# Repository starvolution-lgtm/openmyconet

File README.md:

# OpenMycoNet

Ein Citizen-Science-Projekt im Aufbau: ein weltweit vernetzbares System zur Erfassung
bioelektrischer Signale aus Mykorrhiza- und Pilznetzwerken. Die Aktivität ist messbar — die
Frage ist, was ihre Muster bedeuten.

Website: <https://www.openmyconet.de> · Kontakt und Rechtliches: [Impressum](https://www.openmyconet.de/impressum.html)

Dieses Repository enthält die Software. Diese Seite erklärt für Menschen, wie sie aufgebaut ist
und wie an ihr gearbeitet wird; technische Details stehen in den verlinkten Dateien.

## Was wo liegt

| Teil | Ordner | Was es tut |
|---|---|---|
| **Server** | [`openmyconet_server/`](openmyconet_server/) | Website (fünfsprachig), Anmeldung und Dashboard, Förderer, Chatbot, Datenlabor mit simulierten Daten, Empfang und Prüfung der Messdaten, Verwaltung |
| **Firmware** | [`firmware/`](firmware/README.md) | Software für die Messknoten. Bisher fertig: das Erzeugen, Absichern und Signieren der Datenpakete |
| **Automatische Prüfungen** | [`.github/workflows/`](.github/workflows/) | Tests bei jeder Änderung, Erreichbarkeit der Website alle 15 Minuten |

Nicht hier: die Projektsteuerung (Pläne, Status, Partner, Gebrauchsmuster) liegt bewusst in
einem lokalen, nicht öffentlichen Kontrollzentrum mit eigener verschlüsselter Sicherung.

```mermaid
flowchart LR
    K[Messknoten<br/>ESP32-S3] -- LoRa --> B[Bridge]
    B -- HTTPS, eigener Schlüssel --> S[Server<br/>Flask + PostgreSQL]
    K -. microSD-Import .-> S
    S --> W[Website + Datenlabor]
    S --> D[(Datenbank<br/>sandbox / live)]
    D --> SB[(Sicherung extern,<br/>verschlüsselt)]
```

## Wie eine Änderung entsteht

```mermaid
flowchart LR
    A[Idee / Auftrag] --> C[Code + Tests<br/>lokal grün]
    C --> P[Push auf main]
    P --> CI{Automatische<br/>Prüfungen}
    CI -- rot --> C
    CI -- grün --> ST[Staging<br/>Testumgebung]
    ST --> PR[Produktion<br/>mit Backup + Rückfallweg]
```

1. **Lokal:** Code und Tests entstehen zusammen; alle Tests müssen vor dem Hochladen grün sein.
2. **Automatische Prüfungen bei jedem Push** (GitHub Actions):
   - die komplette Testsuite, einmal mit SQLite und einmal mit PostgreSQL wie im Betrieb,
   - Code-Stil, Sicherheits-Scan des Codes, bekannte Lücken in verwendeten Paketen,
   - Barrierefreiheit, Suchmaschinen-Tauglichkeit und Qualität aller öffentlichen Seiten,
   - Firmware: Normtests der Kryptografie, die Paket-Testvektoren Byte für Byte, und ein
     Kreuztest, bei dem der Server Pakete aus der Firmware liest und nachrechnet.
3. **Staging:** eine vollständige Testumgebung auf demselben Server, eigene Datenbank, verschickt
   nie echte Mails.
4. **Produktion:** nur möglich, wenn die Prüfungen für genau diesen Stand grün sind und Staging
   ihn hat. Vor jedem Datenbank-Umbau wird gesichert; antwortet die Seite danach nicht, wird der
   alte Code automatisch zurückgespielt.

## Sicherheit, in Schichten

- **Website:** Schutz gegen untergeschobene Formulare (CSRF) und eingeschleusten Code (strenge
  Content-Security-Policy), Zwei-Faktor-Anmeldung für die Verwaltung, Begrenzung von
  Wiederholungsversuchen, geprüfte Uploads.
- **Messdaten:** Jedes Paket trägt Prüfsummen, die eine Kette bilden (Lücken und Änderungen
  fallen auf), und eine Signatur des Messknotens (Ed25519); der Server kennt nur öffentliche
  Schlüssel. Datenbank-Rollen sind getrennt: Die Website kann Messdaten weder löschen noch
  genaue Standorte lesen. Strittige Daten werden nie stillschweigend verworfen, sondern
  aufbewahrt.
- **Betrieb:** Zugang zum Server nur mit Schlüssel, Firewall, tägliche verschlüsselte
  Sicherungen außer Haus mit automatischer Wiederherstellungsprobe, Überwachung von außen.
- **Datenschutz:** feste Löschfristen werden automatisch durchgesetzt und stehen so in der
  Datenschutzerklärung.

## Anpassungsfähigkeit

- **Datenbank-Änderungen** laufen als nachvollziehbare Migrationen; ein Test stellt sicher, dass
  Code und Datenbank nie auseinanderlaufen.
- **Versionierte Formate:** Datenpakete und Datenbank-Schemas tragen Versionsnummern; neue
  Versionen kommen hinzu, ohne alte Daten unlesbar zu machen.
- **Simulation und echte Messungen** laufen durch dieselbe Verarbeitung, aber in getrennten
  Bereichen (`sandbox` / `live`).
- **Die Firmware-Kernbibliothek** ist plattformunabhängig und wird auf dem PC gegen den Server
  geprüft — lange bevor eine Platine da ist.

## Für Entwickler

- Server: [`openmyconet_server/CLAUDE.md`](openmyconet_server/CLAUDE.md) (Aufbau, Regeln,
  Tests, Deploy) und die Themen-Dateien in [`openmyconet_server/docs/claude/`](openmyconet_server/docs/claude/)
- Datenpaket-Format: [`openmyconet_server/docs/dateneingang_format_v1.md`](openmyconet_server/docs/dateneingang_format_v1.md)
- Empfangsweg für Bridges: [`openmyconet_server/docs/dateneingang_empfang.md`](openmyconet_server/docs/dateneingang_empfang.md)
- Firmware: [`firmware/README.md`](firmware/README.md)

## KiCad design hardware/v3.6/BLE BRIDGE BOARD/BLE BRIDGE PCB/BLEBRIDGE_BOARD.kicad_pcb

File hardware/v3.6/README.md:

# Hardware V3.6 (fertigungsreif)

Finaler Stand der beiden Platinen **COMBO NODE** (Messknoten) und **BLE BRIDGE**,
Version 3.6 (KiCad-Projekte, Fertigungsdateien, Prüfberichte). Abgelegt am 26.10.2026.

Quelle: Paket `OpenMyCoNet_Project_Completed_Package_Finale_Ver3.6.zip`
(SHA-256 `373a08654455d4fddd7a3f6c591d7695429d6e759cf8f633c875d926a3661b07`),
unverändert entpackt. Weggelassen wurde nur der interne KiCad-Verlauf
`BLE BRIDGE BOARD/BLE BRIDGE PCB/.history/` (ein eingebettetes Git-Verzeichnis vom Juni 2026).

## Für die Bestellung

**Diese beiden BOMs verwenden**, nicht die `bom.csv` in den Unterordnern:

| Datei | Unterschied zur `bom.csv` im Paket |
|---|---|
| `COMBO_NODE_V3.6_bom_korrigiert.csv` | 100 nF (0603): Menge 20 statt 19 (C51 war nicht mitgezählt) |
| `BLEBRIDGE_V3.6_bom_korrigiert.csv` | 10 kΩ (0603): Menge 10 statt 11 (nach Wegfall des zweiten R13) |

Sonst sind die Dateien Zeile für Zeile gleich. Gegengeprüft (26.10.2026): Jede Zeile hat
so viele Bezeichner wie ihre Menge (Node 179, Bridge 99 Bauteile), BOM und
Bestückungsliste (`positions.csv`) enthalten auf beiden Platinen genau dieselben Bauteile.

Gerber und Bohrdaten: `COMBO NODE BOARD/PRODUCTION FILES/production/COMBO_NODE_3.6.zip`
und `BLE BRIDGE BOARD/PRODUCTION FILES/production/BLEBRIDGE_BOARD.zip`.

## Änderungen gegenüber dem Stand vom 23.10.2026

Laut Prüfung (Vergleich der Verdrahtung Pin für Pin, BOM, Bestückungsliste, Layout und Gerber):

- **Node, Puffer:** neuer Baustein U19 (OPA333, SOT-23-5, ca. 17 µA Ruhestrom) als
  Spannungsfolger: Eingang am Teiler R43/R44 (C34), Ausgang über R62 an den Referenzknoten,
  Abblockkondensator C51. U13B arbeitet nur noch für den EC-Empfang, die EC-Messung wird
  nicht mehr verfälscht. In der Netzliste nachvollzogen: U19 Pin 5 an 3.3VA, Pin 2 an GND,
  Pin 3 (+IN) am Teiler, Pin 1 (OUT) und Pin 4 (−IN) verbunden und an R62.
- **Bridge, R13:** nur noch ein R13 (1,18 kΩ an ILIM des BQ24075). Der zweite Widerstand
  an SYSOFF ist entfallen; er zog in der Stellung „Aus“ dauerhaft ca. 0,4 mA aus dem Akku.
  SYSOFF legt der Schalter S1 fest.
- Prüfbericht V3.6: `GUIDE/OpenMycoNet_Architectural_Evolution_Design_Verification_Report_V3.6.docx`.

## Wichtig: TH1 und der Akku

TH1 (10-kΩ-NTC) ist auf **beiden** Platinen nicht bestückt (fehlt in BOM und
Bestückungsliste, steht im Schaltplan aber noch als bestückt, in `designators.csv`
ebenfalls noch aufgeführt). TH1 liegt am TS-Pin des Ladereglers BQ24075 (U4, Pin 1),
an derselben Leitung wie **Pin 2 des Akkusteckers J2** (Belegung +BATT / NTC / GND).

Ohne TH1 misst der Laderegler die Temperatur über den Akkupack. Deshalb:

- **Akkus müssen 3-adrig sein, mit 10-kΩ-NTC (B ≈ 3435) an der mittleren Ader.**
- Ein Akku mit nur 2 Adern lässt TS offen: Der BQ24075 sieht einen Temperaturfehler und
  **lädt nicht**. Dann TH1 bzw. einen festen 10-kΩ-Widerstand doch bestücken.
- Firmware: Die Node misst keine eigene Platinentemperatur. Die Ausgänge CHG und PGOOD
  des BQ24075 hängen auf beiden Platinen nur an Pull-ups (R15/R16), **nicht am ESP32**
  (Netzliste geprüft 27.10.2026). Die Firmware sieht nur die Laderate des MAX17048
  (positiv = lädt) und meldet „lädt“ bzw. „lädt nicht“ im Protokoll. Für eine spätere
  Revision: CHG an einen freien Eingang führen.

## BQ24075: zwei LCSC-Nummern (geklärt)

Der BQ24075 (U4) hat in den beiden BOMs verschiedene LCSC-Nummern: Node `C15464`, Bridge
`C2865459`. Laut Richard (27.10.2026) beabsichtigt: Die Suffixe RGTR und RGTT unterscheiden
nur die Verpackung (Rollengröße), Footprint und Pads sind gleich. Beide Nummern sind für ihre
Platine richtig, die BOMs bleiben so.

## Pin-Merkblatt Firmware (Watchdog, Akkualarm)

`BioComm_Bridge_V3.6_Pinbelegung_Firmware.md` (Stand 27.10.2026), unverändert abgelegt.
Gegen die Netzlisten V3.6 geprüft (27.10.2026), alle Angaben stimmen
(Modul-Pin → GPIO nach Datenblatt ESP32-S3-WROOM-1):

| Signal | Node | Bridge | Netz in der Netzliste |
|---|---|---|---|
| BATT_ALERT | GPIO21 (U6-23) | GPIO47 (U6-24) | MAX17048 U5-5 (ALRT), Pull-up Node R20 / Bridge R32 (10 kΩ), Bridge zusätzlich D3 |
| WCD_SLEEP | GPIO47 (U6-24) | GPIO48 (U6-25) | TPS3851 U7-5 (SET1), Pull-down Node R55 / Bridge R27 (100 kΩ) |
| RST_WDI | GPIO4 (U6-4) | GPIO21 (U6-23) | TPS3851 U7-6 (WDI) |
| LED_ON | – | GPIO41 (U6-34) | über R23 (1 kΩ) an D7 |

Ergänzung für die **Node-Firmware**: Auch die Node hat den TPS3851H33 mit 100 nF an CWD
(C20). Ist ihr Watchdog über GPIO47 eingeschaltet, gilt dort dasselbe Zeitfenster von
rund 323 ms (GPIO4 etwa alle 300 ms umschalten oder vorher abschalten).

## Inhalt

| Ordner | Inhalt |
|---|---|
| `COMBO NODE BOARD/COMBO_NODE/` | KiCad-Projekt Node (Schaltplan-Blätter, Layout) |
| `COMBO NODE BOARD/PRODUCTION FILES/` | Gerber-Zip, BOM, Bestückungsliste, Netzliste (IPC), interaktive BOM, Kaufhinweise für Ersatzteile |
| `COMBO NODE BOARD/REPORTATION/` | Schaltplan-PDF, ERC/DRC-Ergebnisse, Unterlagen zum Watchdog TPS3851 |
| `COMBO NODE BOARD/DOCUMENTATION/` | Bilder der Lagen und Ansichten |
| `BLE BRIDGE BOARD/…` | dasselbe für die Bridge |
| `GUIDE/` | ERC/DRC-Leitfäden beider Platinen, Prüfbericht V3.6 |

Nicht Teil des Deploys: Der Server bekommt nur `openmyconet_server/`.

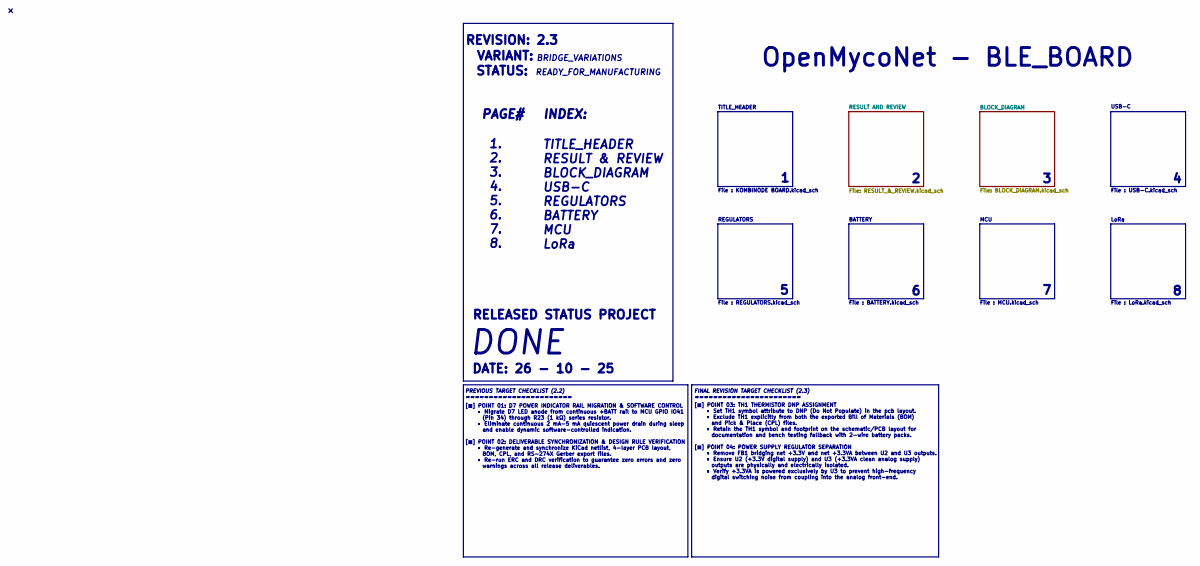
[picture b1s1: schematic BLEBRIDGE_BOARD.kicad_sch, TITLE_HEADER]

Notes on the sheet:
REGULATORS
File : MCU.kicad_sch
File : USB-C.kicad_sch
BATTERY
PAGE#
File : LoRa.kicad_sch
DONE
MCU
File : KOMBINODE BOARD.kicad_sch
USB-C
OpenMycoNet - BLE_BOARD
LoRa
PREVIOUS TARGET CHECKLIST (2.2) =======================
RELEASED STATUS PROJECT
DATE: 26 - 10 - 25
[■] POINT 03: TH1 THERMISTOR DNP ASSIGNMENT • Set TH1 symbol attribute to DNP (Do Not Populate) in the pcb layout. • Exclude TH1 explicitly from both the exported Bill of Materials (BOM) and Pick & Place (CPL) files. • Retain the TH1 symbol and footprint on the schematic/PCB layout for documentatio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
1. 2. 3. 4. 5. 6. 7. 8.
READY_FOR_MANUFACTURING
File : BATTERY.kicad_sch
VARIANT:
REVISION: 2.3
TITLE_HEADER RESULT & REVIEW BLOCK_DIAGRAM USB-C REGULATORS BATTERY MCU LoRa
BRIDGE_VARIATIONS
[■] POINT 01: D7 POWER INDICATOR RAIL MIGRATION & SOFTWARE CONTROL • Migrate D7 LED anode from continuous +BATT rail to MCU GPIO IO41 (Pin 34) through R23 (1 kΩ) series resistor. • Eliminate continuous 2 mA-5 mA quiescent power drain during sleep and enable dynamic software-controlled indication. [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
FINAL REVISION TARGET CHECKLIST (2.3) =======================
STATUS:
TITLE_HEADER
INDEX:
File : REGULATORS.kicad_sch

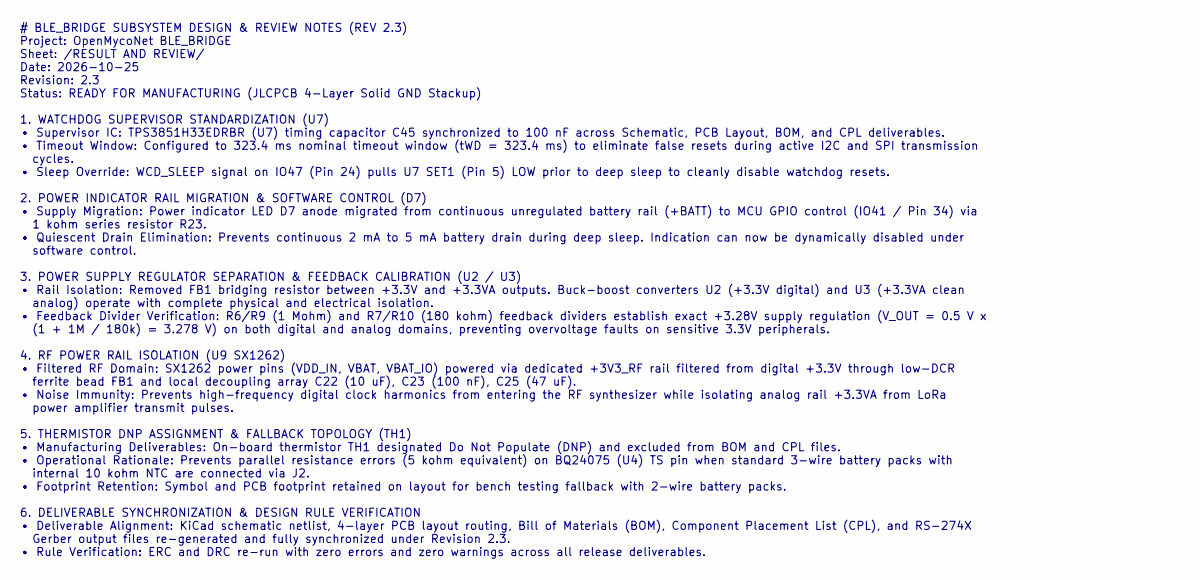
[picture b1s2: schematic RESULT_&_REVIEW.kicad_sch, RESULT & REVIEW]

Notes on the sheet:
# BLE_BRIDGE SUBSYSTEM DESIGN & REVIEW NOTES (REV 2.3) Project: OpenMycoNet BLE_BRIDGE Sheet: /RESULT AND REVIEW/ Date: 2026-10-25 Revision: 2.3 Status: READY FOR MANUFACTURING (JLCPCB 4-Layer Solid GND Stackup) 1. WATCHDOG SUPERVISOR STANDARDIZATION (U7) • Supervisor IC: TPS3851H33EDRBR (U7) timin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

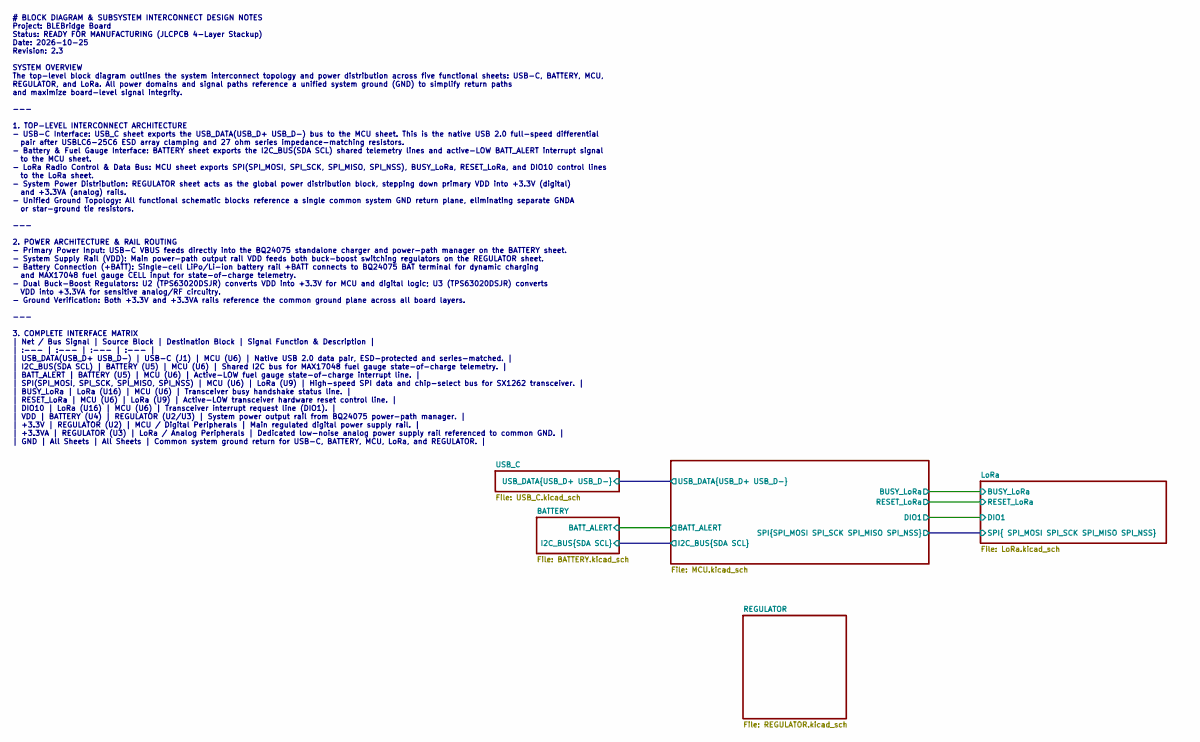
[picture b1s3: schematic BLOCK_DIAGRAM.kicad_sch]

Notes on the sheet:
# BLOCK DIAGRAM & SUBSYSTEM INTERCONNECT DESIGN NOTES Project: BLEBridge Board Status: READY FOR MANUFACTURING (JLCPCB 4-Layer Stackup) Date: 2026-10-25 Revision: 2.3 SYSTEM OVERVIEW The top-level block diagram outlines the system interconnect topology and power distribution across five functional 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

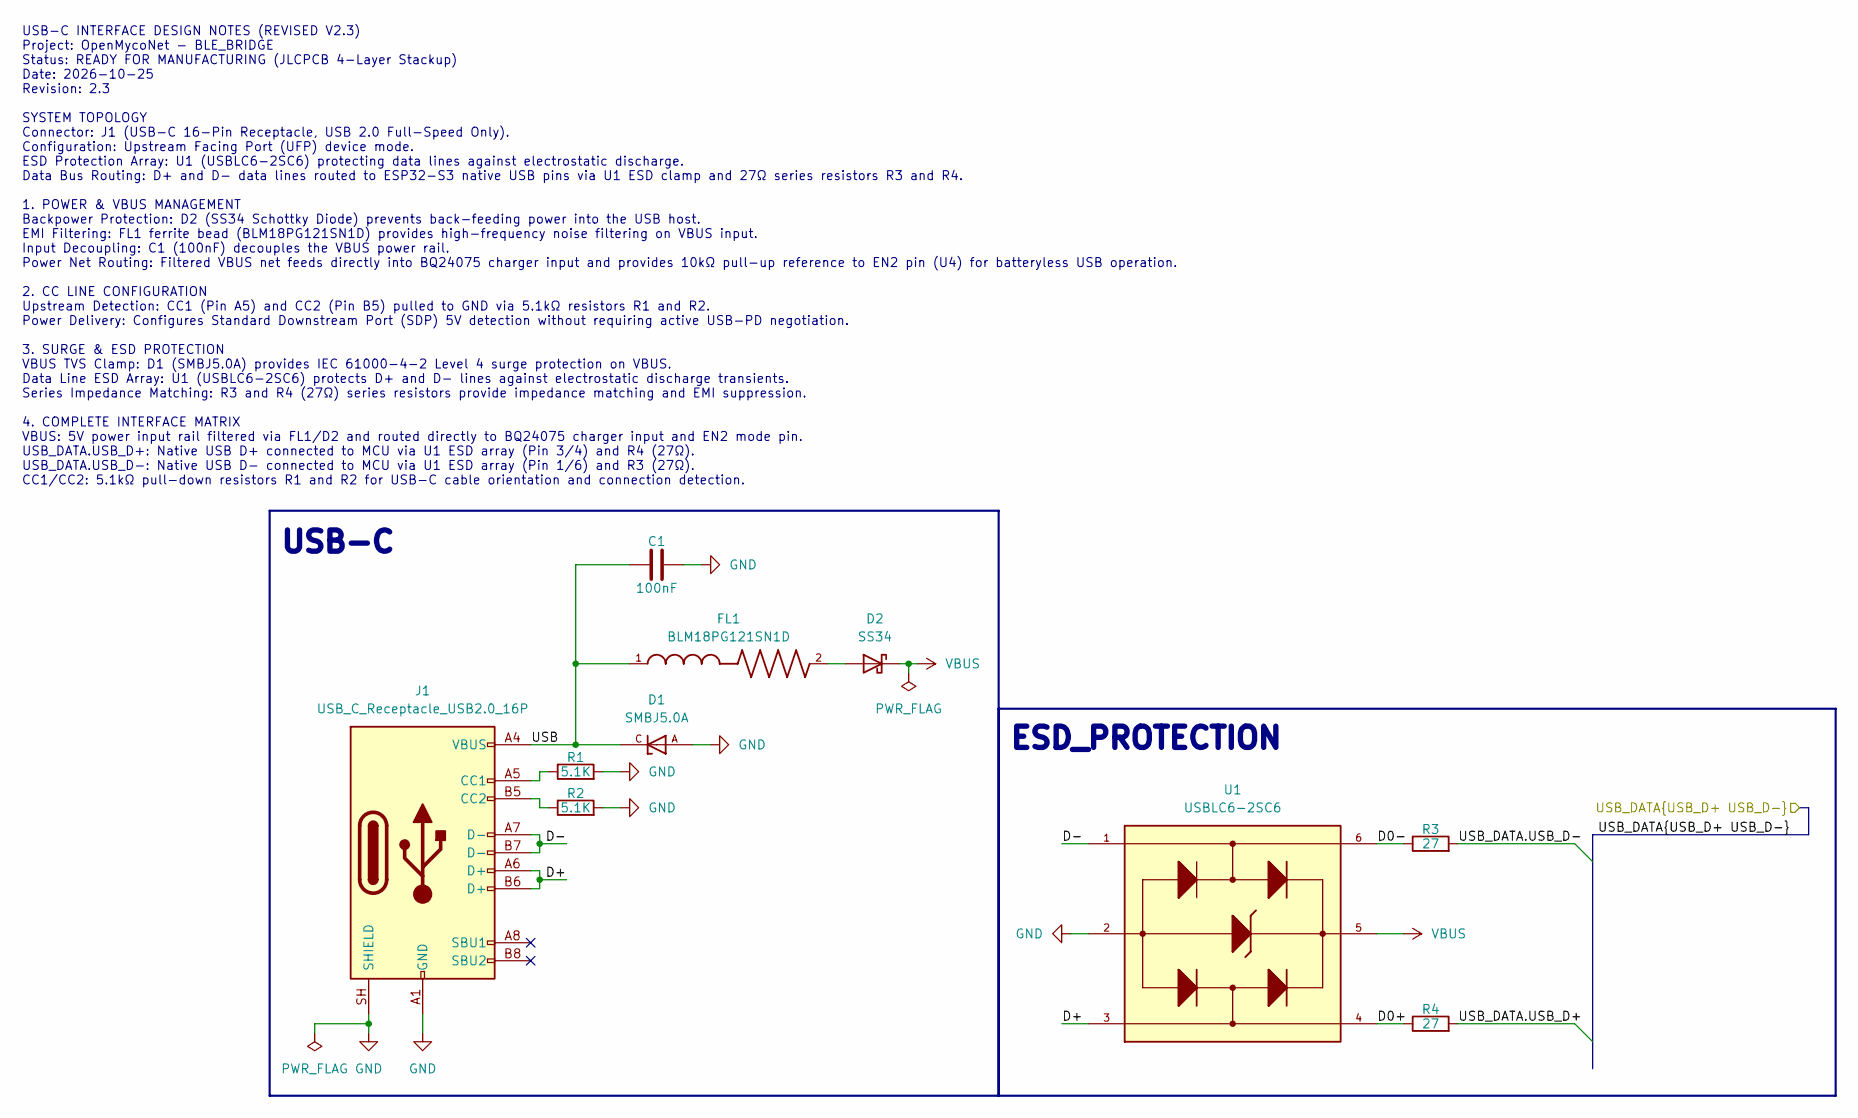
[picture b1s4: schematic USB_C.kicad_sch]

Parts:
C1: 100nF; C_0603_1608Metric
D1: SMBJ5.0A; PARTREV F2102
D2: SS34; D_SMA
FL1: BLM18PG121SN1D; BEADC1608X95N
J1: USB_C_Receptacle_USB2.0_16P; USB_C_Receptacle_GCT_USB4105-xx-A_16P_TopMnt_Horizontal
R1, R2: 5.1K; R_0402_1005Metric
R3, R4: 27; R_0402_1005Metric
U1: USBLC6-2SC6

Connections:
/BLOCK_DIAGRAM//USB_DATA.USB_D+: R4.2; also elsewhere on the board
/BLOCK_DIAGRAM//USB_DATA.USB_D-: R3.2; also elsewhere on the board
/BLOCK_DIAGRAM/USB_C/D0+: R4.1, U1.4
/BLOCK_DIAGRAM/USB_C/D0-: R3.1, U1.6
/BLOCK_DIAGRAM/USB_C/D+: J1.A6 (D+), J1.B6 (D+), U1.3
/BLOCK_DIAGRAM/USB_C/D-: J1.A7 (D-), J1.B7 (D-), U1.1
/BLOCK_DIAGRAM/USB_C/USB: C1.1, D1.C, FL1.1, J1.A4 (VBUS), J1.A9 (VBUS), J1.B4 (VBUS), J1.B9 (VBUS)
GND: C1.2, D1.A, J1.A1 (GND), J1.A12 (GND), J1.B1 (GND), J1.B12 (GND), J1.SH (SHIELD), R1.2, R2.2, U1.2; also elsewhere on the board
unnamed: D2.2 (A), FL1.2
unnamed: J1.A5 (CC1), R1.1
unnamed: J1.B5 (CC2), R2.1
VBUS: D2.1 (K), U1.5; also elsewhere on the board

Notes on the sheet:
USB-C INTERFACE DESIGN NOTES (REVISED V2.3) Project: OpenMycoNet - BLE_BRIDGE Status: READY FOR MANUFACTURING (JLCPCB 4-Layer Stackup) Date: 2026-10-25 Revision: 2.3 SYSTEM TOPOLOGY Connector: J1 (USB-C 16-Pin Receptacle, USB 2.0 Full-Speed Only). Configuration: Upstream Facing Port (UFP) device mo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
ESD_PROTECTION
USB-C

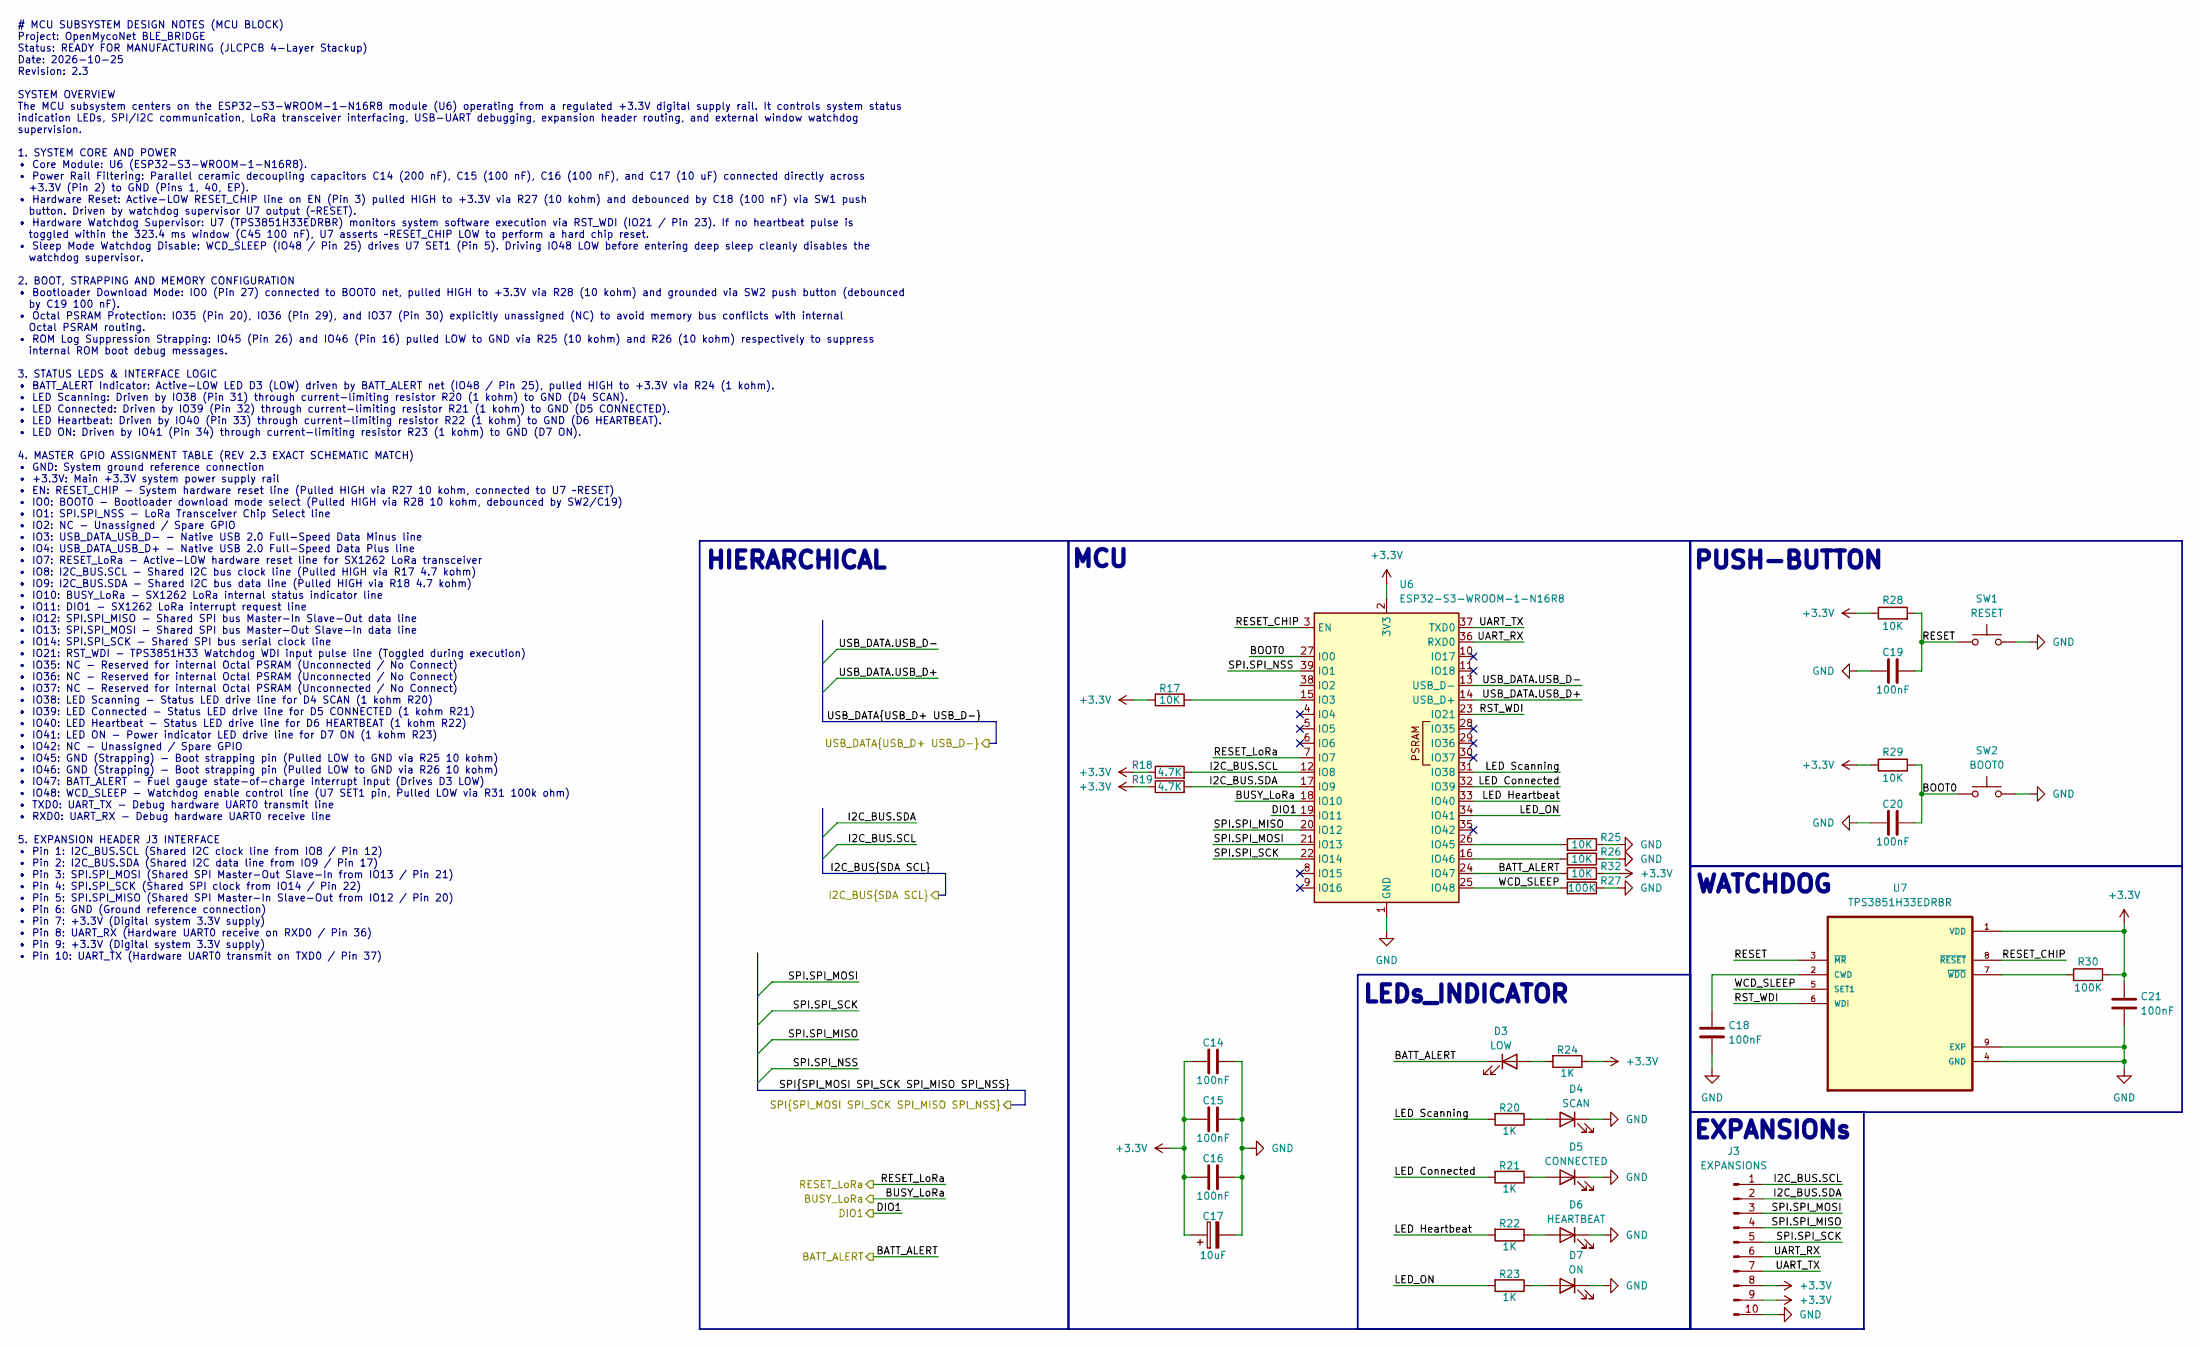
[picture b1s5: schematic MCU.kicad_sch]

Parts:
C14, C15, C16, C18, C19, C20, C21: 100nF; C_0603_1608Metric
C17: 10uF; CP_EIA-3216-18_Kemet-A
D3: LOW; LED_1206_3216Metric
D4: SCAN; LED_1206_3216Metric
D5: CONNECTED; LED_1206_3216Metric
D6: HEARTBEAT; LED_1206_3216Metric
D7: ON; LED_1206_3216Metric
J3: EXPANSIONS; PinHeader_2x05_P2.54mm_Vertical_SMD
R17, R25, R26, R28, R29, R32: 10K; R_0603_1608Metric
R18, R19: 4.7K; R_0603_1608Metric
R20, R21, R22, R23, R24: 1K; R_0603_1608Metric
R27, R30: 100K; R_0603_1608Metric
SW1: RESET; SW_SPST_B3U-1000P
SW2: BOOT0; SW_SPST_B3U-1000P
U6: ESP32-S3-WROOM-1-N16R8; ESP32-S3-WROOM-1
U7: TPS3851H33EDRBR; IC_DRV8601DRBT

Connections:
+3.3V: C14.1, C15.1, C16.1, C17.1, C21.1, J3.8, J3.9, R17.1, R18.1, R19.1, R24.1, R28.1, R29.1, R30.2, R32.1, U6.2 (3V3), U7.1 (VDD); also elsewhere on the board
/BLOCK_DIAGRAM//BATT_ALERT: D3.1 (K), R32.2, U6.24 (IO47); also elsewhere on the board
/BLOCK_DIAGRAM//BOOT0: C20.2, R29.2, SW2.1, U6.27 (IO0)
/BLOCK_DIAGRAM//BUSY_LoRa: U6.18 (IO10); also elsewhere on the board
/BLOCK_DIAGRAM//DIO1: U6.19 (IO11); also elsewhere on the board
/BLOCK_DIAGRAM//I2C_BUS.SCL: J3.1, R18.2, U6.12 (IO8); also elsewhere on the board
/BLOCK_DIAGRAM//I2C_BUS.SDA: J3.2, R19.2, U6.17 (IO9); also elsewhere on the board
/BLOCK_DIAGRAM//LED Connected: R21.2, U6.32 (IO39)
/BLOCK_DIAGRAM//LED Heartbeat: R22.2, U6.33 (IO40)
/BLOCK_DIAGRAM//LED Scanning: R20.2, U6.31 (IO38)
/BLOCK_DIAGRAM//LED_ON: R23.2, U6.34 (IO41)
/BLOCK_DIAGRAM//RESET: C19.2, R28.2, SW1.1, U7.3 (~MR)
/BLOCK_DIAGRAM//RESET_CHIP: U6.3 (EN), U7.8 (~RESET)
/BLOCK_DIAGRAM//RESET_LoRa: U6.7 (IO7); also elsewhere on the board
/BLOCK_DIAGRAM//RST_WDI: U6.23 (IO21), U7.6 (WDI)
/BLOCK_DIAGRAM//SPI.SPI_MISO: J3.4, U6.20 (IO12); also elsewhere on the board
/BLOCK_DIAGRAM//SPI.SPI_MOSI: J3.3, U6.21 (IO13); also elsewhere on the board
/BLOCK_DIAGRAM//SPI.SPI_NSS: U6.39 (IO1); also elsewhere on the board
/BLOCK_DIAGRAM//SPI.SPI_SCK: J3.5, U6.22 (IO14); also elsewhere on the board
/BLOCK_DIAGRAM//UART_RX: J3.6, U6.36 (RXD0)
/BLOCK_DIAGRAM//UART_TX: J3.7, U6.37 (TXD0)
/BLOCK_DIAGRAM//USB_DATA.USB_D+: U6.14 (USB_D+); also elsewhere on the board
/BLOCK_DIAGRAM//USB_DATA.USB_D-: U6.13 (USB_D-); also elsewhere on the board
/BLOCK_DIAGRAM//WCD_SLEEP: R27.2, U6.25 (IO48), U7.5 (SET1)
GND: C14.2, C15.2, C16.2, C17.2, C18.2, C19.1, C20.1, C21.2, D4.1 (K), D5.1 (K), D6.1 (K), D7.1 (K), J3.10, R25.1, R26.1, R27.1, SW1.2, SW2.2, U6.1 (GND), U6.40 (GND), U6.41 (GND), U7.4 (GND), U7.9 (EXP), U7.10 (EXP), U7.11 (EXP), U7.12 (EXP), U7.13 (EXP); also elsewhere on the board
unnamed: D3.2 (A), R24.2
unnamed: D4.2 (A), R20.1
unnamed: D5.2 (A), R21.1
unnamed: D6.2 (A), R22.1
unnamed: D7.2 (A), R23.1
unnamed: R17.2, U6.15 (IO3)
unnamed: R25.2, U6.26 (IO45)
unnamed: R26.2, U6.16 (IO46)
unnamed: C18.1, U7.2 (CWD)
unnamed: R30.1, U7.7 (~WDO)

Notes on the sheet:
WATCHDOG
HIERARCHICAL
PUSH-BUTTON
EXPANSIONs
# MCU SUBSYSTEM DESIGN NOTES (MCU BLOCK) Project: OpenMycoNet BLE_BRIDGE Status: READY FOR MANUFACTURING (JLCPCB 4-Layer Stackup) Date: 2026-10-25 Revision: 2.3 SYSTEM OVERVIEW The MCU subsystem centers on the ESP32-S3-WROOM-1-N16R8 module (U6) operating from a regulated +3.3V digital supply rail. 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
LEDs_INDICATOR
MCU

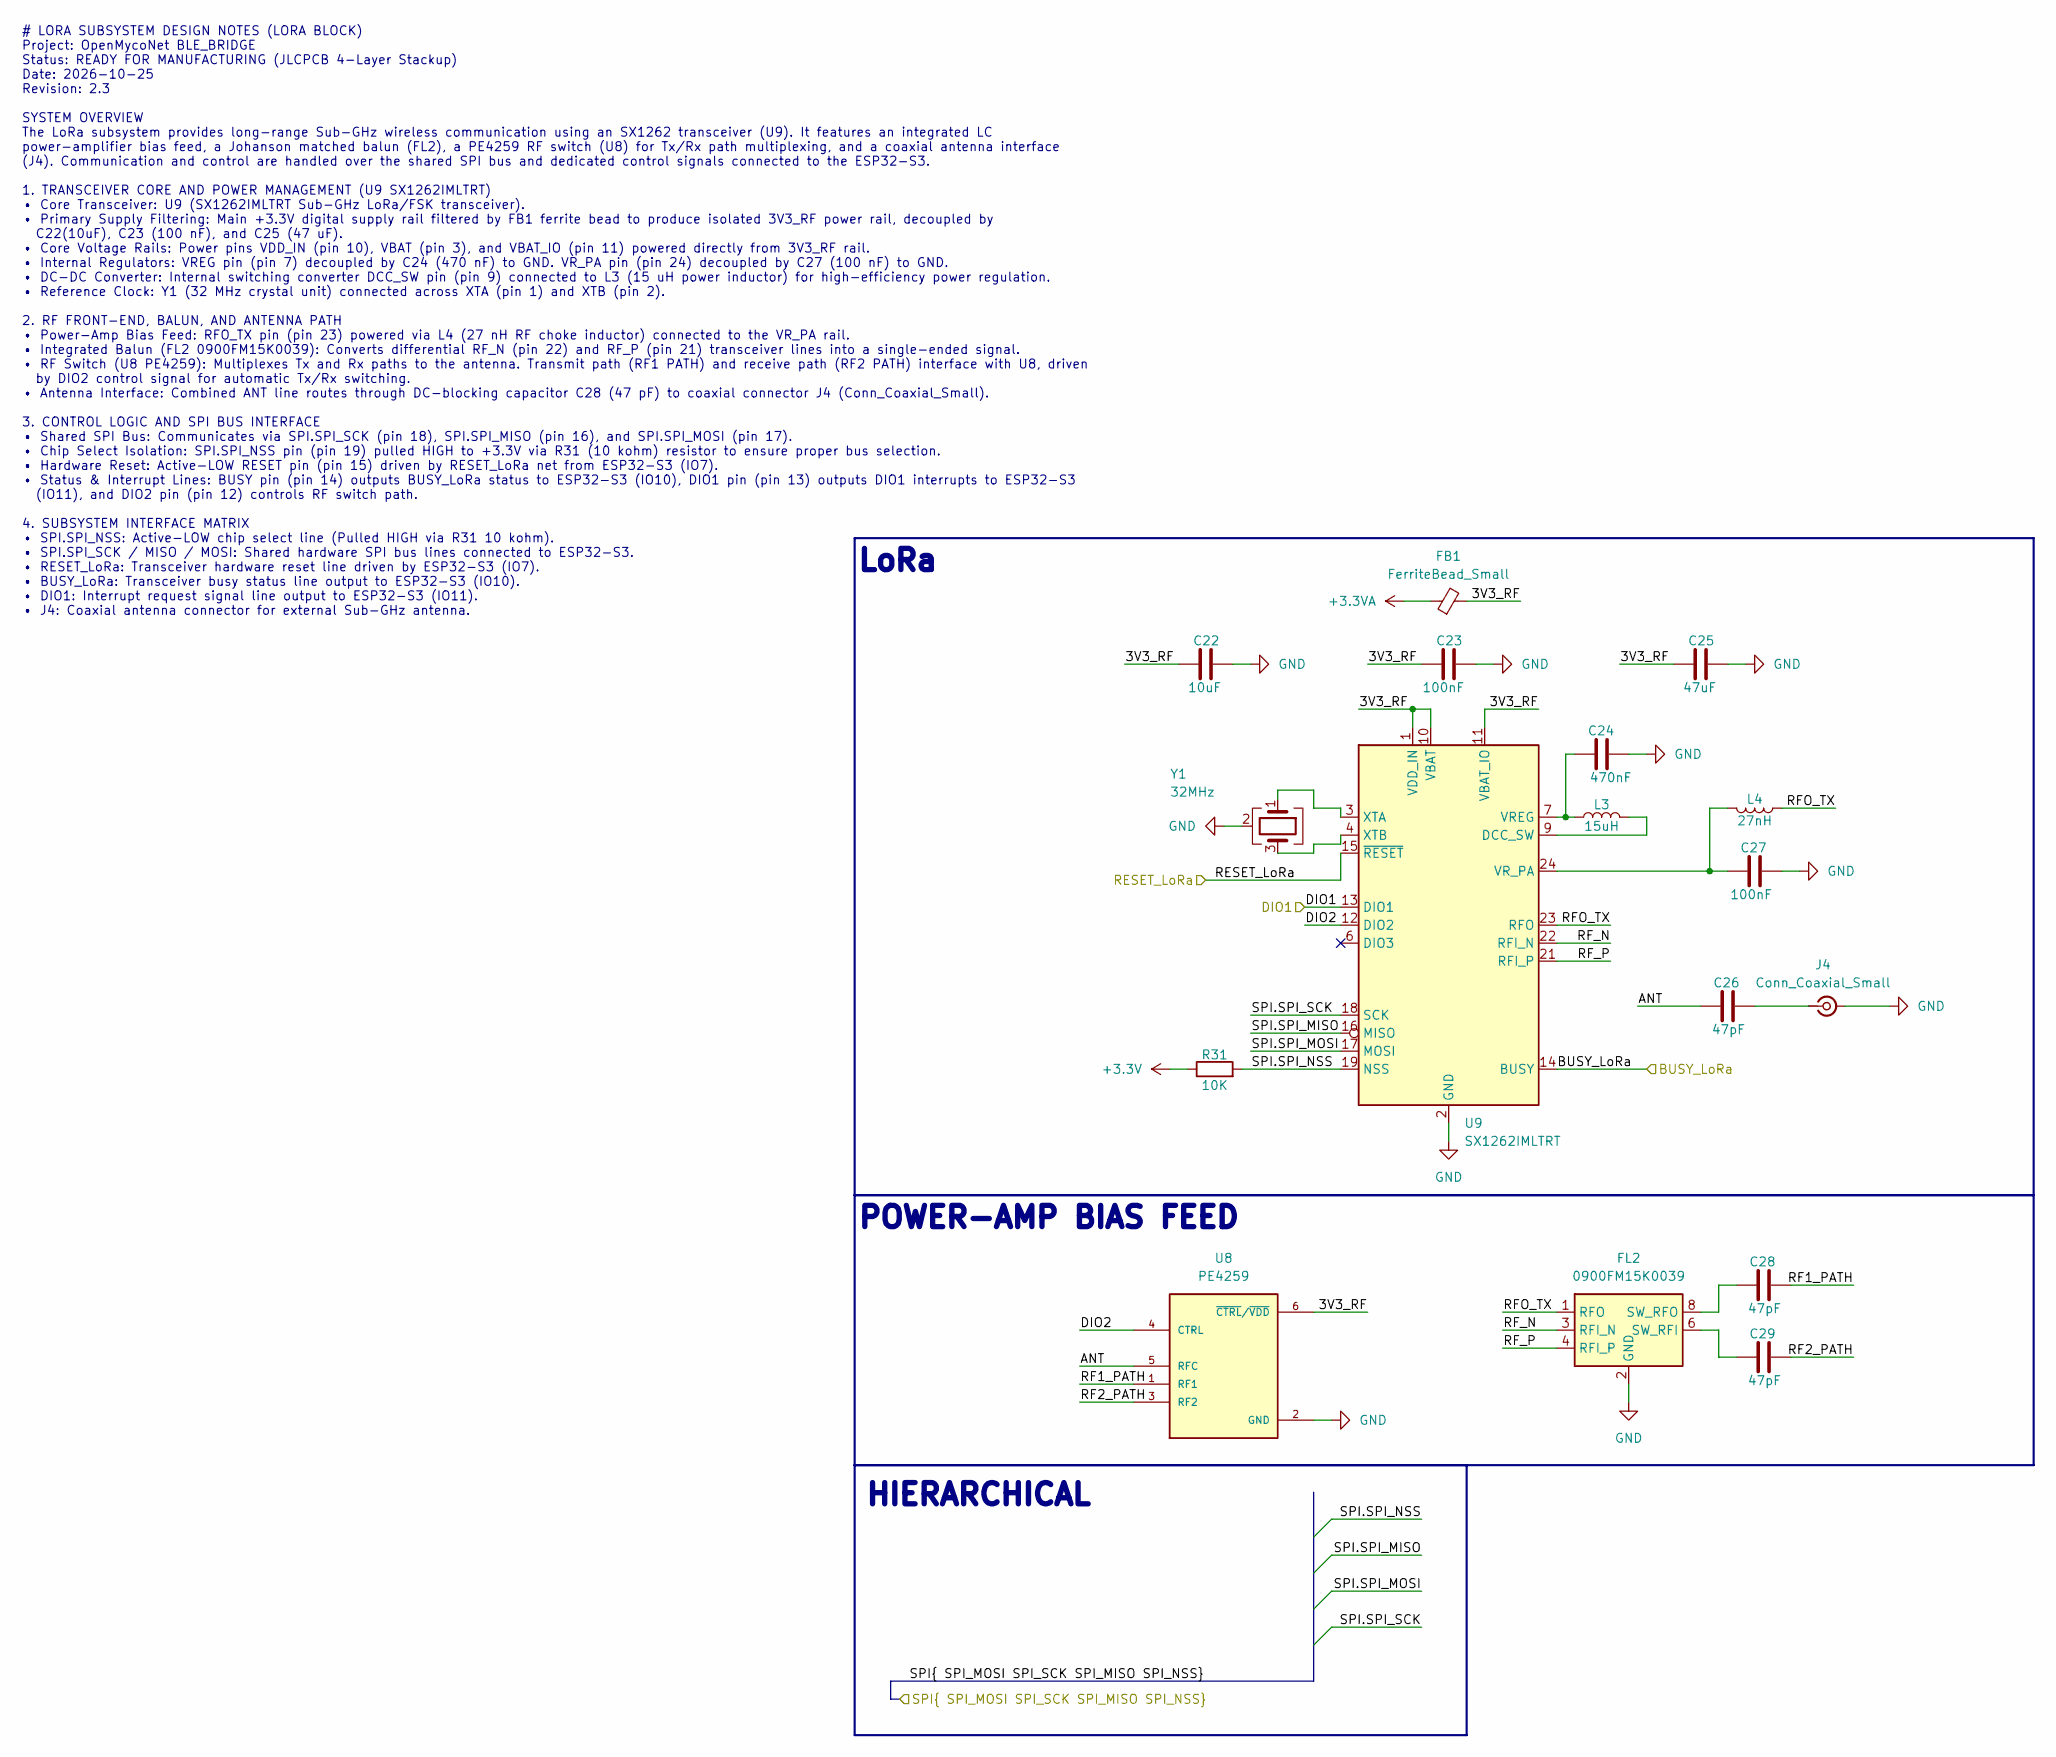
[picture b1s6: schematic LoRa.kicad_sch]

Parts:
C22: 10uF; C_1206_3216Metric
C23: 100nF; C_1206_3216Metric
C24: 470nF; C_1206_3216Metric
C25: 47uF; C_1206_3216Metric
C26, C28, C29: 47pF; C_0805_2012Metric
C27: 100nF; C_0805_2012Metric
FB1: FerriteBead_Small; L_0805_2012Metric
FL2: 0900FM15K0039; Balun_Johanson_0900FM15K0039
J4: Conn_Coaxial_Small; U.FL_Hirose_U.FL-R-SMT-1_Vertical
L3: 15uH; L_APV_APH1040
L4: 27nH; L_0603_1608Metric
R31: 10K; R_0603_1608Metric
U8: PE4259; SOT65P215X110-6N
U9: SX1262IMLTRT; QFN-24-1EP_4x4mm_P0.5mm_EP2.6x2.6mm
Y1: 32MHz; Crystal_SMD_2520-4Pin_2.5x2.0mm

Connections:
+3.3V: R31.1; also elsewhere on the board
+3.3VA: FB1.1; also elsewhere on the board
/BLOCK_DIAGRAM//BUSY_LoRa: U9.14 (BUSY); also elsewhere on the board
/BLOCK_DIAGRAM//DIO1: U9.13 (DIO1); also elsewhere on the board
/BLOCK_DIAGRAM//RESET_LoRa: U9.15 (~RESET); also elsewhere on the board
/BLOCK_DIAGRAM//SPI.SPI_MISO: U9.16 (MISO); also elsewhere on the board
/BLOCK_DIAGRAM//SPI.SPI_MOSI: U9.17 (MOSI); also elsewhere on the board
/BLOCK_DIAGRAM//SPI.SPI_NSS: R31.2, U9.19 (NSS); also elsewhere on the board
/BLOCK_DIAGRAM//SPI.SPI_SCK: U9.18 (SCK); also elsewhere on the board
/BLOCK_DIAGRAM/LoRa/3V3_RF: C22.1, C23.1, C25.1, FB1.2, U8.6 (~CTRL/~VDD), U9.1 (VDD_IN), U9.10 (VBAT), U9.11 (VBAT_IO)
/BLOCK_DIAGRAM/LoRa/ANT: C26.1, U8.5 (RFC)
/BLOCK_DIAGRAM/LoRa/DIO2: U8.4 (CTRL), U9.12 (DIO2)
/BLOCK_DIAGRAM/LoRa/RF1_PATH: C28.2, U8.1 (RF1)
/BLOCK_DIAGRAM/LoRa/RF2_PATH: C29.2, U8.3 (RF2)
/BLOCK_DIAGRAM/LoRa/RFO_TX: FL2.1 (RFO), L4.1, U9.23 (RFO)
/BLOCK_DIAGRAM/LoRa/RF_N: FL2.3 (RFI_N), U9.22 (RFI_N)
/BLOCK_DIAGRAM/LoRa/RF_P: FL2.4 (RFI_P), U9.21 (RFI_P)
GND: C22.2, C23.2, C24.1, C25.2, C27.2, FL2.2 (GND), FL2.5 (GND), FL2.7 (GND), FL2.9 (GND), FL2.10 (GND), J4.2 (Ext), U8.2 (GND), U9.2 (GND), U9.5 (GND), U9.8 (GND), U9.20 (GND), U9.25 (GND), Y1.2 (G), Y1.4 (G); also elsewhere on the board
unnamed: C29.1, FL2.6 (SW_RFI)
unnamed: C28.1, FL2.8 (SW_RFO)
unnamed: C26.2, J4.1 (In)
unnamed: L3.2, U9.9 (DCC_SW)
unnamed: C24.2, L3.1, U9.7 (VREG)
unnamed: C27.1, L4.2, U9.24 (VR_PA)
unnamed: U9.3 (XTA), Y1.1
unnamed: U9.4 (XTB), Y1.3

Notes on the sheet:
HIERARCHICAL
LoRa
POWER-AMP BIAS FEED
# LORA SUBSYSTEM DESIGN NOTES (LORA BLOCK) Project: OpenMycoNet BLE_BRIDGE Status: READY FOR MANUFACTURING (JLCPCB 4-Layer Stackup) Date: 2026-10-25 Revision: 2.3 SYSTEM OVERVIEW The LoRa subsystem provides long-range Sub-GHz wireless communication using an SX1262 transceiver (U9). It features an i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

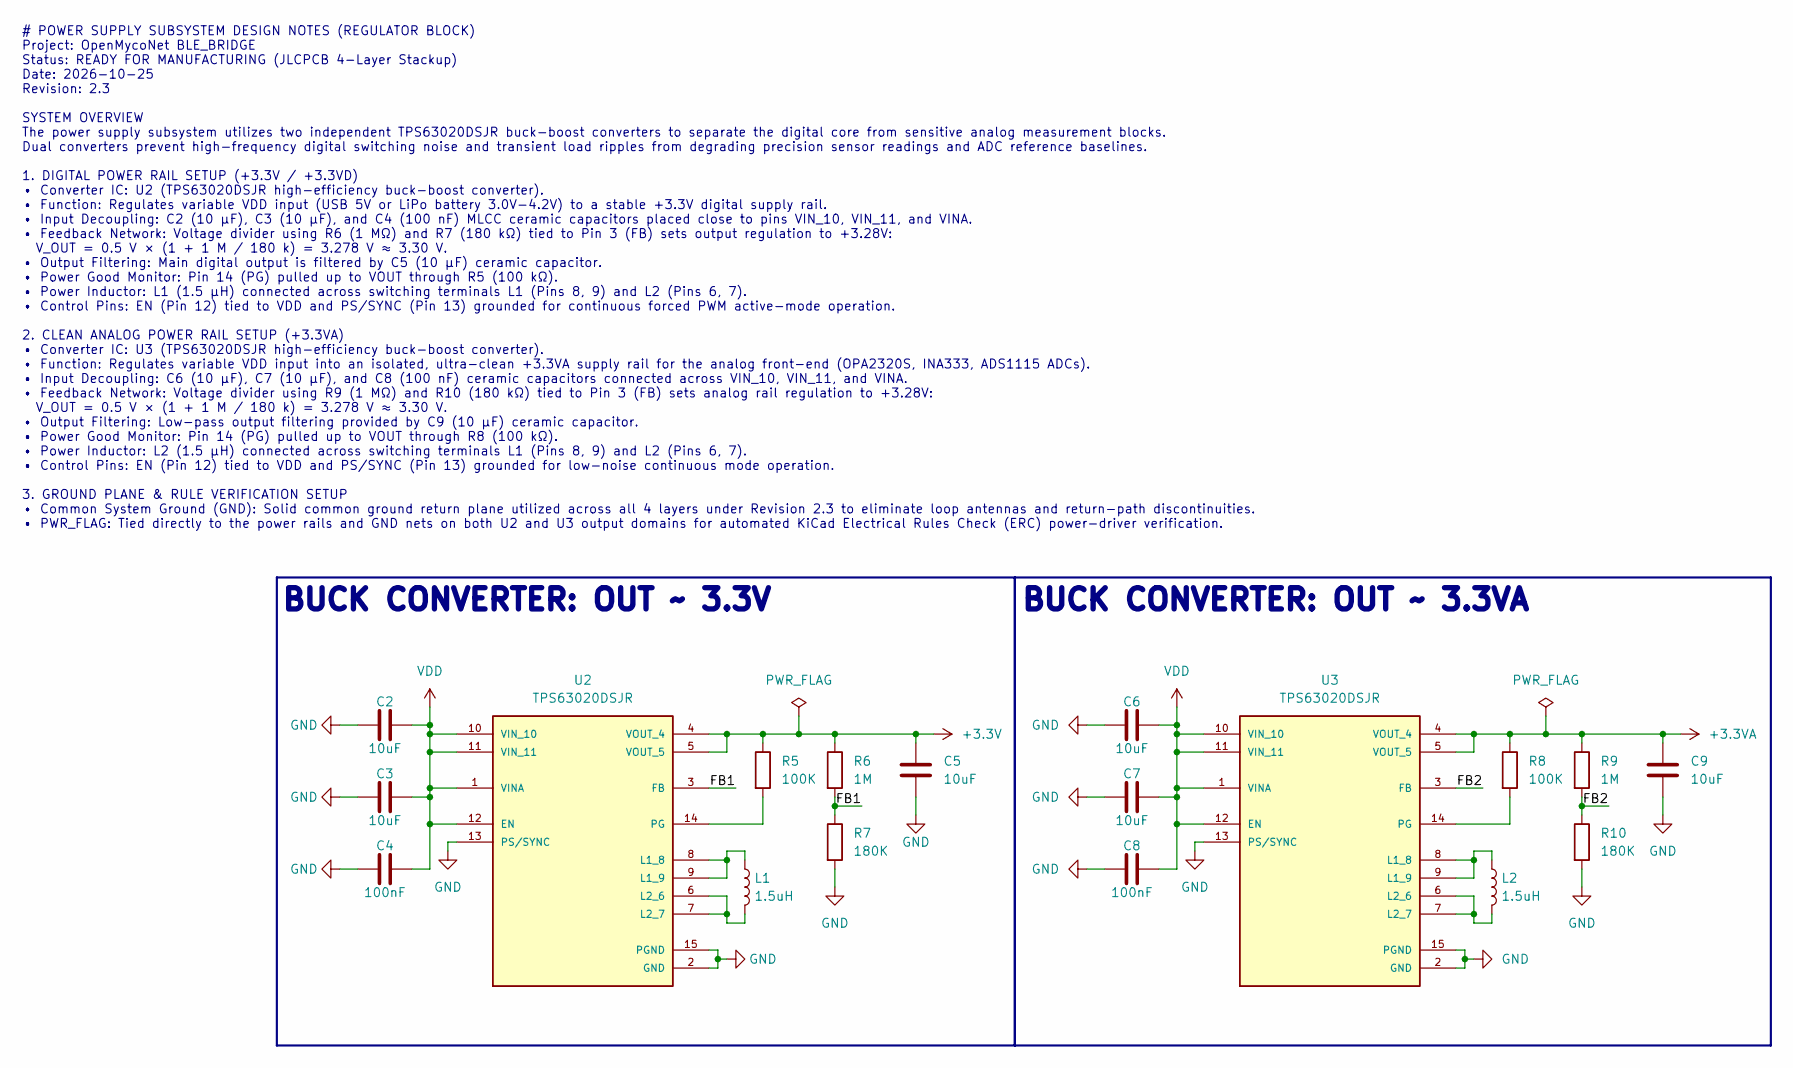
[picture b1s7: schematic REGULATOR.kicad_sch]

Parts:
C2, C3, C5, C6, C7, C9: 10uF; C_0805_2012Metric
C4, C8: 100nF; C_0603_1608Metric
L1, L2: 1.5uH; L_APV_APH0630
R5, R8: 100K; R_0603_1608Metric
R6, R9: 1M; R_0603_1608Metric
R7, R10: 180K; R_0603_1608Metric
U2, U3: TPS63020DSJR; IC_TPS63020DSJT; PARTREV I

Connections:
+3.3V: C5.2, R5.1, R6.1, U2.4 (VOUT_4), U2.5 (VOUT_5); also elsewhere on the board
+3.3VA: C9.2, R8.1, R9.1, U3.4 (VOUT_4), U3.5 (VOUT_5); also elsewhere on the board
/BLOCK_DIAGRAM/REGULATOR/FB1: R6.2, R7.1, U2.3 (FB)
/BLOCK_DIAGRAM/REGULATOR/FB2: R9.2, R10.1, U3.3 (FB)
GND: C2.2, C3.2, C4.2, C5.1, C6.2, C7.2, C8.2, C9.1, R7.2, R10.2, U2.2 (GND), U2.13 (PS/SYNC), U2.15 (PGND), U3.2 (GND), U3.13 (PS/SYNC), U3.15 (PGND); also elsewhere on the board
unnamed: L1.1, U2.8 (L1_8), U2.9 (L1_9)
unnamed: L1.2, U2.6 (L2_6), U2.7 (L2_7)
unnamed: R5.2, U2.14 (PG)
unnamed: L2.1, U3.8 (L1_8), U3.9 (L1_9)
unnamed: L2.2, U3.6 (L2_6), U3.7 (L2_7)
unnamed: R8.2, U3.14 (PG)
VDD: C2.1, C3.1, C4.1, C6.1, C7.1, C8.1, U2.1 (VINA), U2.10 (VIN_10), U2.11 (VIN_11), U2.12 (EN), U3.1 (VINA), U3.10 (VIN_10), U3.11 (VIN_11), U3.12 (EN); also elsewhere on the board

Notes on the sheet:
BUCK CONVERTER: OUT ~ 3.3V
BUCK CONVERTER: OUT ~ 3.3VA
# POWER SUPPLY SUBSYSTEM DESIGN NOTES (REGULATOR BLOCK) Project: OpenMycoNet BLE_BRIDGE Status: READY FOR MANUFACTURING (JLCPCB 4-Layer Stackup) Date: 2026-10-25 Revision: 2.3 SYSTEM OVERVIEW The power supply subsystem utilizes two independent TPS63020DSJR buck-boost converters to separate the digi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
